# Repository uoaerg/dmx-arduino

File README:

This repository contains the full source code and hardware designs for the
Arduino shield used for teaching DMX at the University of Aberdeen. The Arduino
Mega 2560 compatible shield allows an Ardunio to operate as either a DMX bus
master or slave.

The dmx-arduino Board (Rev I and II) was designed by Cyril Danilesvski in 2014.
The software was written and was updated by Tom Jones, 2015-2017.
The software is updated by Gorry Fairhurst, 2020-2023.

# Uploading the code

Open the Arduino project from dmxcontroller/dmxcontroller.ino.

Import the libraries from the libraries/ into the Arduino IDE. It is
important that you do not allow the Aruduino IDE to update these libraries.

Compile and upload.

# Operation

Program mode and DMX addressing are controlled by the 12 dip switches on the
main sheild PCB. Program status is indicated using the three LEDs in most
program modes or using additional LEDs on the DE9 connector in other modes.

There is a default program that can is used in any empty slot in the program
mode. This program will only blink the green LED.

The RED LED on the board provides the DMX status. If valid DMX data has been seen
on the bus, then DMXTIMEOUT will flash the red LED. If no valid DMX data has
been seen for 1 sec this LED will be lit solidly. This functionality operates 
outside the control of any of the programs.

When the main loop of the program detects a change in program mode the green
LED will be flashed momentarily. This flash can be difficult to see when
turning off DIP switches, but is easier to see when turning on DIP switches.

## DIP Switches

The 12 DIP switches form a 12-bit number with the MSB starting with switch 1.
The program mode is encoded in the top three bits of the DIP switches and the
DMX address is encoded in the bottom 9 bits.

                  1 1 1
1 2 3 4 5 6 7 8 9 0 1 2
P P P D D D D D D D D D

The software has 8 modes (3 bits):

0 - DMX Controller
1 - Digital Output Control
2 - PWM Control 
3 - Servo Control
4 - Neopixel Strip Control
5 - Stepper Motor Control
6 - Unused.
7 - Long Strip Control

0 - DMX Controller Mode
	The programmed DMX address will be displayed on the 8 DE2PINs with the 9th
	bit displayed on the green LED.

	If a DMX address of 0 is selected on the DIP switches, the slot sequence
	0x55 0xFF 0x0F 0xF0 will be output for the first four DMX slots.

	In controller mode, the program will read from a 10K pot connected to POT_PIN. The
	10bit value from the ADC will be scaled (divided by 4) to fit with in a DMX
	byte. If this value is greater than 128, then the yellow LED will be lit. The
	scaled value from the pot. will be written to the DMX bus at the slot set by the DMX
	address.

1 - Digital control
	Eight DMX channels will be read from the bus. If the DMX value is
	greater than 128, then the corresponding DE2PIN will set high.

	The yellow LED shows the status of channel 1.

2 - PWM Control 
	The first eight DMX channels will be read from the bus. The corresponding
	DE2PINs will be given a PWM values from the DMX value.

	The yellow LED shows the status of channel 1.

3 - Servo Control
	The servo will be driven to a position based upon the DMX value at the selected
	DMX address.

	The yellow LED shows the status of channel 1.

4 - Neopixel Control
	An encoded colour value will be read from a set of DMX slots. Each *byte*
	encodes an RGB value. These values are split out then set to an attached
	LED strip using the Neopixel Library. These are sent as a time division
	multiplex as 3 serialised 8-bit colour values using the assigned pin.

	The yellow LED shows the status of channel 1.

5 - Stepper Motor Control
	An encoded stepper motor control value will be read from a set of DMX slots. 
	A set of 2 slots control the speed of rotation of the stepper motor and direction.
	A set of 2 slots sets an index position, and then controls the relative angle to 
	the indexed position. The rotation controls also control the speed of movement.

7 - Long Neopixel Control
	As mode 5, but with the timing adjusted to allow a long strip to be driven.

	The yellow LED shows the status of channel 1.

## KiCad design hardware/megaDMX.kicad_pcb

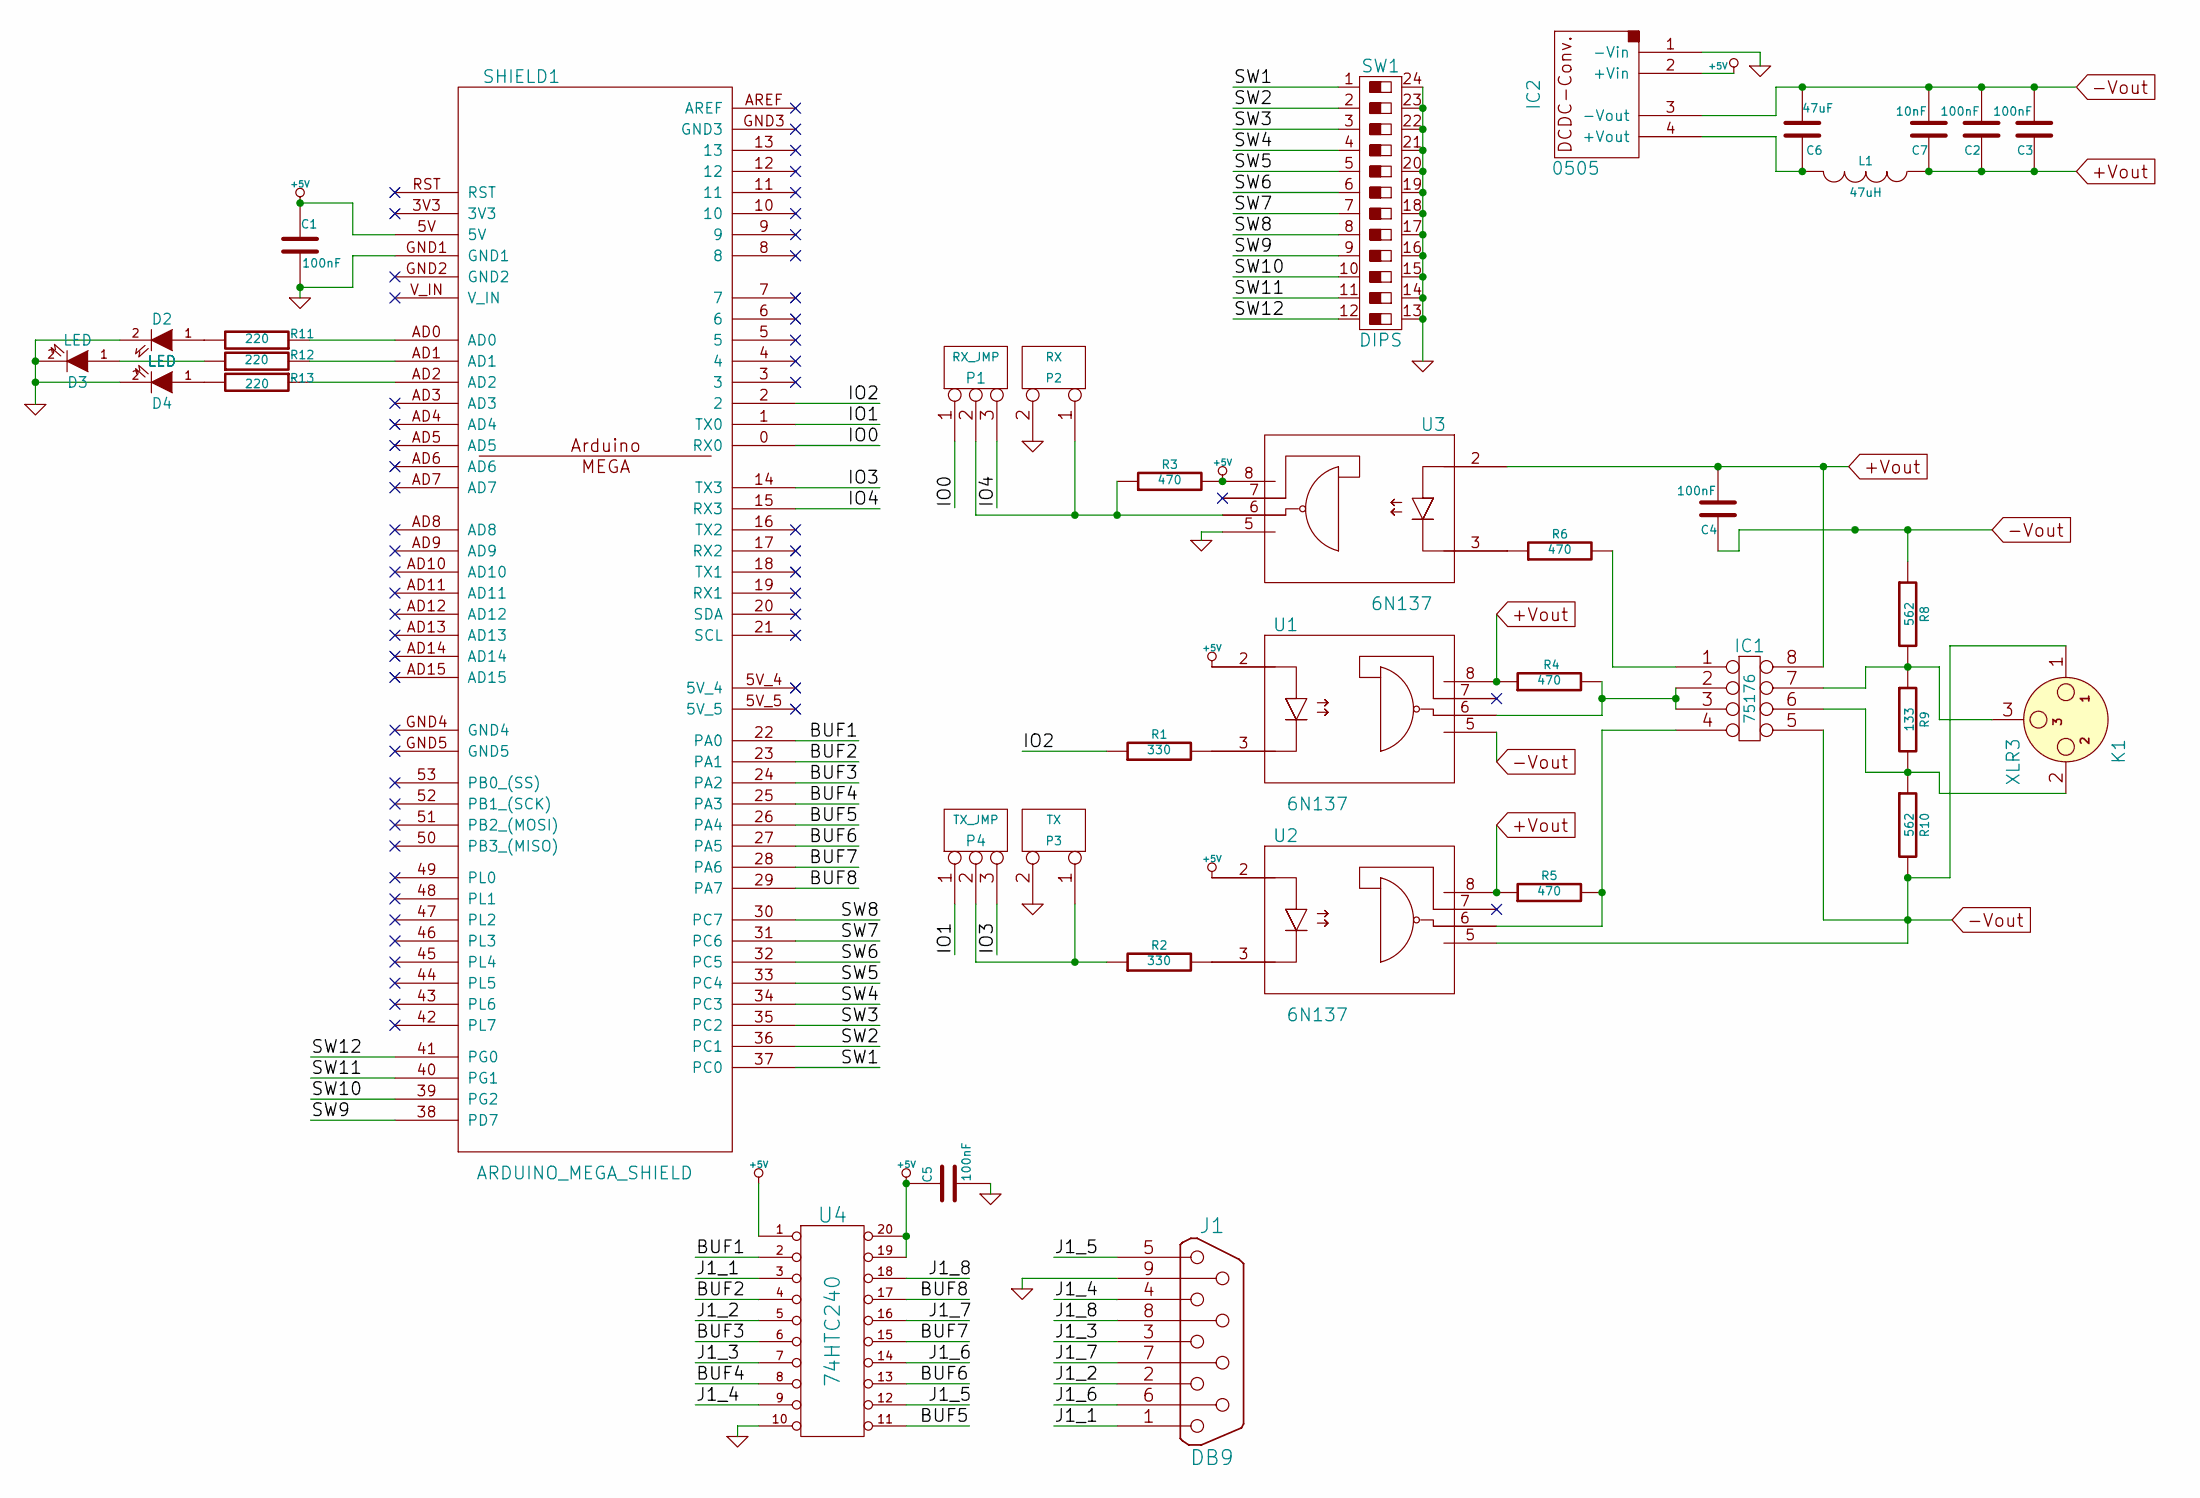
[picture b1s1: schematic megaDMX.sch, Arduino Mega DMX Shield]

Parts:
C1, C2, C3, C4, C5: 100nF
C6: 47uF
C7: 10nF
D2, D3, D4: LED
IC1: 75176
IC2: 0505
J1: DB9
K1: XLR3
L1: 47uH
P1: RX_JMP
P2: RX
P3: TX
P4: TX_JMP
R1, R2: 330
R3, R4, R5, R6: 470
R8, R10: 562
R9: 133
R11, R12, R13: 220
SHIELD1: ARDUINO_MEGA_SHIELD
SW1: DIPS
U1, U2, U3: 6N137
U4: 74HTC240

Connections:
+5V: C1.1, C5.1, IC2.2 (+Vin), R3.2, SHIELD1.5V, U1.2, U2.2, U3.8, U4.1, U4.19, U4.20
+Vout: C2.1, C3.1, C4.2, C7.1, IC1.8, L1.1, R4.1, R5.1, U1.8, U2.8, U3.2
-Vout: C2.2, C3.2, C4.1, C6.2, C7.2, IC1.5, IC2.3 (-Vout), K1.1, R8.1, R10.2, U1.5, U2.5
/BUF1: SHIELD1.22 (PA0), U4.2
/BUF2: SHIELD1.23 (PA1), U4.4
/BUF3: SHIELD1.24 (PA2), U4.6
/BUF4: SHIELD1.25 (PA3), U4.8
/BUF5: SHIELD1.26 (PA4), U4.11
/BUF6: SHIELD1.27 (PA5), U4.13
/BUF7: SHIELD1.28 (PA6), U4.15
/BUF8: SHIELD1.29 (PA7), U4.17
/IO0: P1.1, SHIELD1.0 (RX0)
/IO1: P4.1, SHIELD1.1 (TX0)
/IO2: R1.1, SHIELD1.2
/IO3: P4.3, SHIELD1.14 (TX3)
/IO4: P1.3, SHIELD1.15 (RX3)
/J1_1: J1.1, U4.3
/J1_2: J1.2, U4.5
/J1_3: J1.3, U4.7
/J1_4: J1.4, U4.9
/J1_5: J1.5, U4.12
/J1_6: J1.6, U4.14
/J1_7: J1.7, U4.16
/J1_8: J1.8, U4.18
/SW1: SHIELD1.37 (PC0), SW1.1
/SW2: SHIELD1.36 (PC1), SW1.2
/SW3: SHIELD1.35 (PC2), SW1.3
/SW4: SHIELD1.34 (PC3), SW1.4
/SW5: SHIELD1.33 (PC4), SW1.5
/SW6: SHIELD1.32 (PC5), SW1.6
/SW7: SHIELD1.31 (PC6), SW1.7
/SW8: SHIELD1.30 (PC7), SW1.8
/SW9: SHIELD1.38 (PD7), SW1.9
/SW10: SHIELD1.39 (PG2), SW1.10
/SW11: SHIELD1.40 (PG1), SW1.11
/SW12: SHIELD1.41 (PG0), SW1.12
GND: C1.2, C5.2, D2.2 (K), D3.2 (K), D4.2 (K), IC2.1 (-Vin), J1.9, P2.2 (PM), P3.2 (PM), SHIELD1.GND1, SW1.13, SW1.14, SW1.15, SW1.16, SW1.17, SW1.18, SW1.19, SW1.20, SW1.21, SW1.22, SW1.23, SW1.24, U3.5, U4.10
unnamed: R11.1, SHIELD1.AD0
unnamed: D2.1 (A), R11.2
unnamed: D4.1 (A), R13.2
unnamed: D3.1 (A), R12.1
unnamed: R12.2, SHIELD1.AD1
unnamed: R13.1, SHIELD1.AD2
unnamed: C6.1, IC2.4 (+Vout), L1.2
unnamed: P3.1, P4.2 (PM), R2.1
unnamed: P1.2 (PM), P2.1, R3.1, U3.6
unnamed: IC1.1, R6.2
unnamed: IC1.2, IC1.3, R4.2, U1.6
unnamed: IC1.6, K1.2, R9.2, R10.1
unnamed: IC1.7, K1.3, R8.2, R9.1
unnamed: R6.1, U3.3
unnamed: IC1.4, R5.2, U2.6
unnamed: R2.2, U2.3
unnamed: R1.2, U1.3

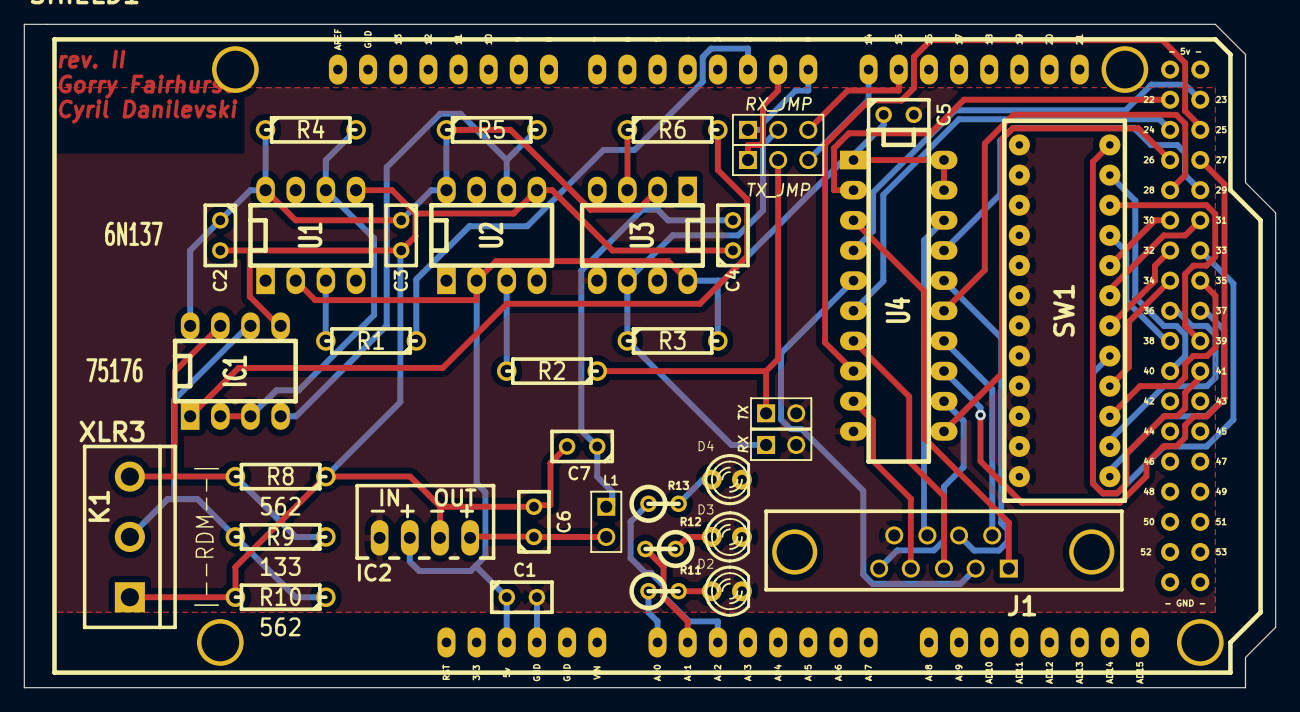
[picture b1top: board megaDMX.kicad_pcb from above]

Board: 2 copper layers, 105.4 x 55.9 mm, 37 parts (0 on the bottom side), 54 nets.

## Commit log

2017-02-22 Import of dmx-arduino from private svn
2017-02-22 update the readme
2017-03-11 Disable scope debug in hte DMX Library
    Build fails with scope debug enabled, this feature from the original library has never worked for me. It is still worth trying to get this to work in the future. The frame trigger should be useful on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
2018-02-23 print git rev on boot
2018-02-23 On mode change to testmode, write 0 for each slot value. This stops DMXSerial truncating the frame around slot 30
2018-12-04 Import definitions for rev 3 of the board
2019-02-22 correct logic for board revisions
2019-02-26 Remove debug print
2019-02-26 Remove delays from main loop
2019-02-26 A first whack at a stepper mode
2019-05-16 Raise the minimum delay
    The motor can be eased into a higher rate than it can start at. Pin the
    maximum speed (higher minimum delay) to a level we can always start at.
2019-07-29 Final stepper support
2023-03-15 Comment about Neopixel timing
    Added note about long LED strips taking time to serialise the TDM output to the Neopixel;
2023-03-16 Do we call DMXSerial.init(DMXReceiver); each loop?
2023-03-16 Fix Neopixel Panel addr >510
    Also re-initiallise DMX each loop;
2023-03-16 Number of Neopixel LEDs = 32
2023-03-16 Release version 0.5
2023-08-16 Update dmxcontroller.ino
    Starting code reveiw 2023
2023-08-16 Update dmxboard.h
    Added new release name
2023-08-16 Update dmxcontroller.ino
    GF
2023-08-16 Update dmxboard.h
    GF
2023-08-16 Update dmxcontroller.ino
    Added support for long LED strips for address >=508
2023-08-16 Update dmxcontroller.ino
    Added ReadStart...
2023-08-16 Update dmxcontroller.ino
    Issue with DMX ports on Mega
2023-08-17 Update dmxcontroller.ino
    Added long LED mode
2023-08-17 Update README
    Update Aug 2023
2023-08-18 Update dmxcontroller.ino
    Changes: This unmangles the logic in the stepper motor code and creates a long neoxpixel mode.
    Both need to be tested.
2023-08-18 Update dmxcontroller.ino
    Update with working stepper
2023-08-18 Update pins.h
    Updated LEDLENGTH here.
2023-08-18 Update dmxcontroller.ino
    Final version for flashing of boards Aug 2023
2023-08-18 Update pins.h
    Aug 2023
2023-08-18 Update pins.h
    1.0 Aug 2023, GF
2023-08-20 Re-load pins.h
2023-08-20 Added more printing at start dmxcontroller.ino
2023-08-20 Added pot pin2 to pins.h
2023-08-20 Added potpin2 dmxcontroller.ino
2023-08-20 Update dmxboard.h to include title as comment
2023-08-20 Added local support for stepper control dmxcontroller.ino
2023-08-20 Update pins.h to include mode analague inputs
2023-08-20 Update dmxcontroller.ino added intialise POT_PINS
2023-08-20 Update dmxcontroller.ino local-use defined
2023-08-20 Update dmxcontroller.ino to add local mode
2023-08-21 Update dmxcontroller.ino at university for reflash
2023-08-21 Update dmxcontroller.ino
    Define void setup(void); to be compatible with a newer IDE
